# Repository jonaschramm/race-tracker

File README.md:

Custom PCB data logger for motorcycle racing: GPS position + IMU motion data,
logged to a microSD card, with an e-Paper status display. Built around an
ESP32-S3 (WiFi/BT built in) so it can also stream/sync over WiFi.

## Current version: V3 (ESP32-S3)

**This is the active, current board.** Everything else in this repo (see
[History / older versions](#history--older-versions) below) is superseded —
kept for reference only, not under active development.

```
RaceTracker.kicad_prj/V3 ESP32/RaceTracker_v3/RaceTracker_v3.kicad_pro
```

Open that project file in KiCad (10.0.5 or newer) — schematic
(`RaceTracker_v3.kicad_sch`) and PCB (`RaceTracker_v3.kicad_pcb`) are
alongside it.

### Status

- Schematic: ERC clean (0 violations).
- PCB: fully routed by hand, `kicad-cli pcb drc --severity-all` → 0 errors
  (a handful of expected warnings only — see below).
- Board: 4-layer, ~56×66mm with rounded corner bosses for 4× M2 mounting
  holes.
- BOM: all 44 parts have a manufacturer part number and LCSC code (or
  DigiKey, where LCSC doesn't carry the part) in the schematic symbol
  properties — see `bom/bom.csv`.

**Known, expected DRC warnings (not bugs):**
- `lib_footprint_mismatch` on J1, J5, J6, SW1, U1 — these footprints were
  deliberately hand-adjusted to match real component pad geometry (pulled
  from the parts' own datasheets/reference designs) rather than the stock
  KiCad library footprint. **Do not run "Update Footprint from Library" on
  these** — it would silently overwrite the verified geometry.

### Key components

| Function | Part |
|---|---|
| MCU (WiFi + BT) | ESP32-S3-WROOM-1-N8 (U1) |
| IMU (6-axis) | Würth WSEN-ISDS (U4) |
| GPS | external module via J3 (2.54mm header, I2C) — no onboard GPS |
| Storage | microSD (J4) |
| Display | e-Paper via J6 (8-pin header) |
| Charging | MCP73831 Li-Ion charger (U2) + USB-C (J1) |
| 3.3V rail | AP2112K-3.3 LDO (U3) |
| Debug | UART via J5 (4-pin header) |

Pin-header connectors (J3, J5, J6) have their pin functions silkscreened
next to each pin so nothing gets miswired when the board is in hand without
the schematic open.

### 3D preview

Rendered straight from the board file (`kicad-cli pcb render`). A ready-to-embed,
interactive 3D model (quantized GLB, 3.4 MB — Draco was tried first but needs an
external decoder that not every embedding context can reach) lives at
[`RaceTracker.kicad_prj/V3 ESP32/RaceTracker_v3/3d/RaceTracker_v3.glb`](RaceTracker.kicad_prj/V3%20ESP32/RaceTracker_v3/3d/RaceTracker_v3.glb) —
drop it into a [`<model-viewer>`](https://modelviewer.dev/) tag on any webpage to let
visitors spin the board around (also works in AR on phones). More stills in
`assets/renders/`.

### Open items

Not yet done — flagging so nothing is assumed finished:

1. **RF review** — the ESP32-S3's on-board antenna keepout is respected on
   the PCB, but nobody with hands-on RF experience has reviewed the
   placement. Espressif's own guideline calls for **≥15mm clearance between
   the antenna and any metal** (enclosure, shielding) — the two mounting
   holes closest to the antenna (top-left/top-right) are only ~3mm away, so
   **use nylon/plastic M2 screws there**, not metal.
2. **Enclosure / mechanical design** — no current mechanical spec for a
   case; board dimensions have changed several times, don't reuse an old one.
3. **3D models / "finished" 3D view** — not started.
4. Two BOM values are assumptions, not confirmed: D2/D3 LED colors (set to
   red/green — schematic didn't specify a color) and SW1's exact MPN
   (couldn't verify its physical dimensions against the datasheet).
5. 27 pads show as "no net" against the schematic's auto-generated
   placeholder nets — reviewed at a glance as genuinely-unused pins
   (GPIO headroom, USB SBU lines), not individually re-verified.

## Repo layout

```
RaceTracker.kicad_prj/
├── *.kicad_sch, RaceTracker.kicad_pcb   ← V1 (SAMD21 + onboard GPS/WiFi modules) — historical
├── V3 ESP32/RaceTracker_v3/             ← V3 (ESP32-S3) — CURRENT, see above
└── V3 ESP32/tools/                      ← pcbnew scripting helpers used while building V3
v2-simple/                                ← V2 (SAMD21, simplified, external GPS/WiFi) — abandoned mid-layout, superseded by V3
reference/eagle/                          ← imported Eagle symbols (Arduino MKR WiFi 1010) used as a source for V1/V2 parts
bom/bom.csv                               ← current BOM with MPN/LCSC/pricing data (V3)
```

### History / older versions

- **V1** (`RaceTracker.kicad_prj/*.kicad_sch` at the repo root, tag
  `v1-full`): original design — Arduino MKR WiFi 1010 (SAMD21) + separate
  u-blox ZED-F9P RTK GPS module + MPU-6050 IMU. Fully routed, but heavier
  and pricier than needed for the actual use case.
- **V2 / `v2-simple`**: a pivot to drop the onboard GPS/WiFi modules in
  favor of external pluggable headers, still on the SAMD21. Placement-only;
  routing was never finished before the project moved to V3's ESP32-S3
  (which has WiFi/BT built in, removing the need for a separate radio
  module entirely). Kept for reference; not maintained.

## Branches

`main` tracks the current state (V3). Historical exploration happened on
`v2-simple` — merged into `main` and not separately maintained going forward.

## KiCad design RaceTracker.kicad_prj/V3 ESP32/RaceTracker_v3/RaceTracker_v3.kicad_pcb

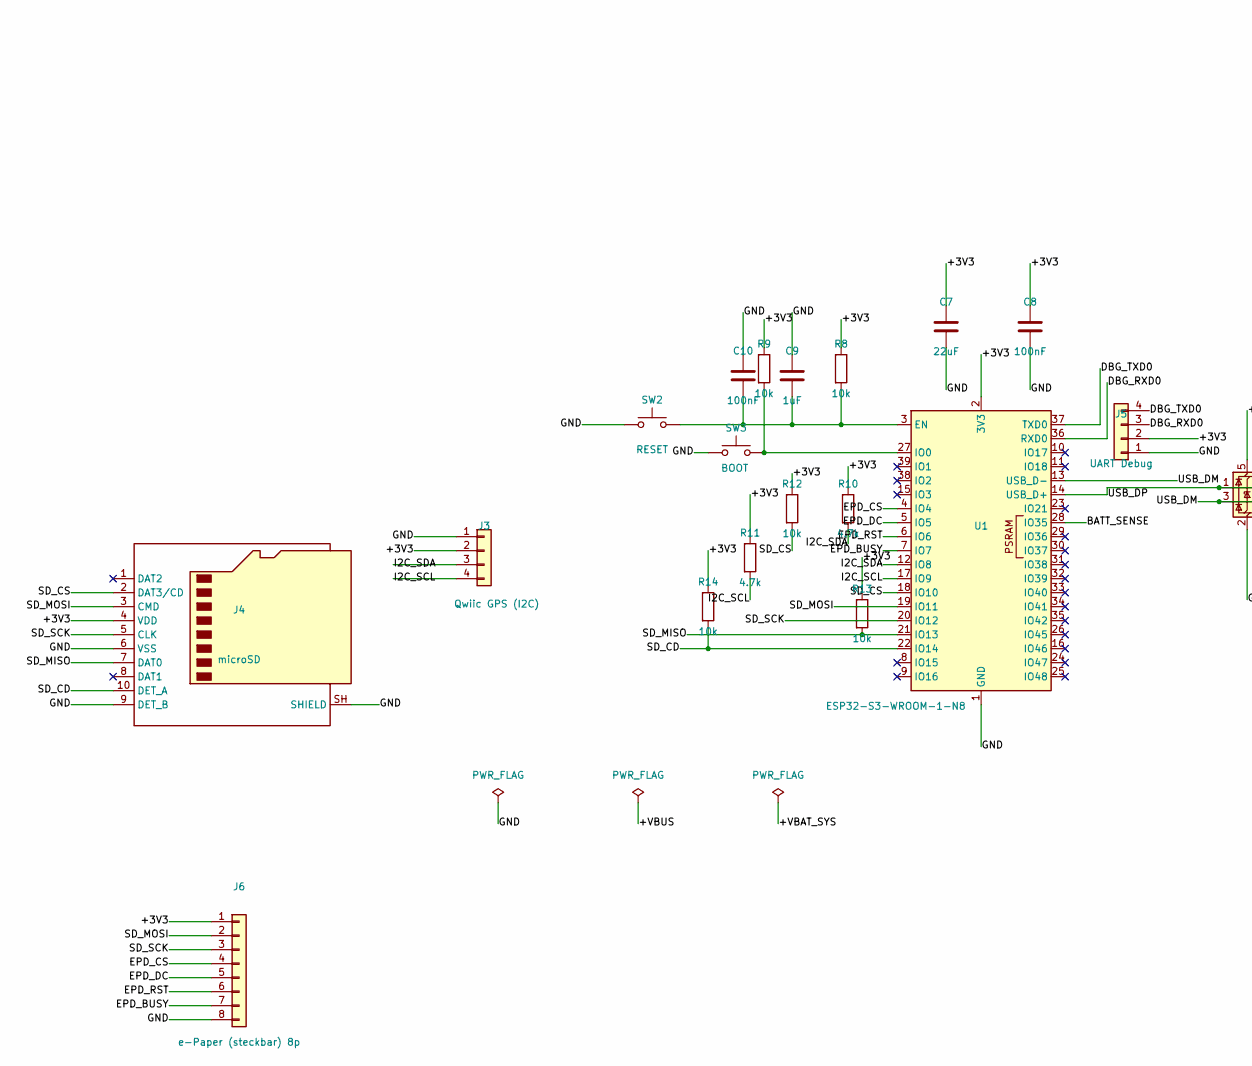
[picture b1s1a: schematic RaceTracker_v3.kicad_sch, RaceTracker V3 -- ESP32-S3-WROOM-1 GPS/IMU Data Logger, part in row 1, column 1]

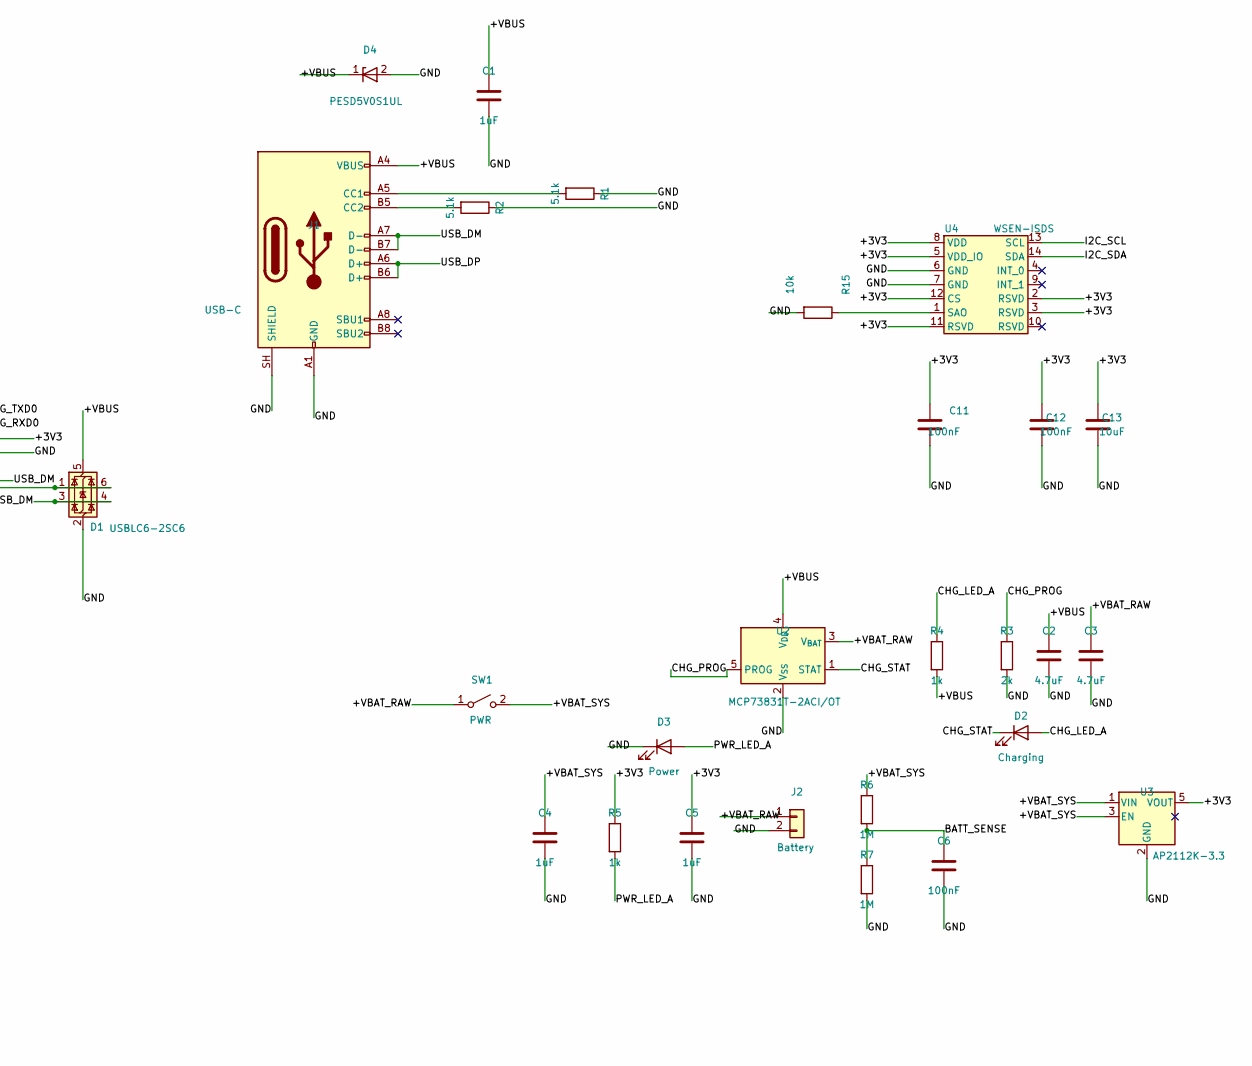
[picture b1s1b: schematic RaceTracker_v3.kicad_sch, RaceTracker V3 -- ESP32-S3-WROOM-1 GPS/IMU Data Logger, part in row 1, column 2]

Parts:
C1, C4, C5, C9: 1uF; C_0603_1608Metric; MPN CL10A105KB8NNNC; LCSC C15849
C2, C3: 4.7uF; C_0603_1608Metric; MPN CL10A475KO8NNNC; LCSC C19666
C6, C8, C10, C11, C12: 100nF; C_0603_1608Metric; MPN CC0603KRX7R9BB104; LCSC C14663
C7: 22uF; C_0805_2012Metric; MPN CL21A226MAQNNNE; LCSC C45783
C13: 10uF; C_0805_2012Metric; MPN CL21A106KAYNNNE; LCSC C15850
D1: USBLC6-2SC6; SOT-23-6; MPN USBLC6-2SC6; LCSC C2687116
D2: Charging; LED_0603_1608Metric; MPN XL-1608SURC-06; LCSC C965799
D3: Power; LED_0603_1608Metric; MPN XL-1608UGC-04; LCSC C965804
D4: PESD5V0S1UL; D_SOD-882; MPN PESD5V0S1UL; LCSC C85402
J1: USB-C; USB_C_Receptacle_HRO_TYPE-C-31-M-12; MPN TYPE-C-31-M-12; LCSC C165948
J2: Battery; JST_PH_S2B-PH-SM4-TB_1x02-1MP_P2.00mm_Horizontal; MPN S2B-PH-SM4-TB(LF)(SN); LCSC C295747
J3: Qwiic GPS (I2C); PinHeader_1x04_P2.54mm_Vertical; MPN PZ254V-11-04P; LCSC C2691448
J4: microSD; microSD_HC_Molex_104031-0811; MPN 104031-0811; LCSC C585350
J5: UART Debug; PinHeader_1x04_P2.54mm_Vertical; MPN PZ254V-11-04P; LCSC C2691448
J6: e-Paper (steckbar) 8p; PinHeader_1x08_P2.54mm_Vertical; MPN PZ254V-11-08P; LCSC C492407
R1, R2: 5.1k; R_0603_1608Metric; MPN 0603WAF5101T5E; LCSC C23186
R3: 2k; R_0603_1608Metric; MPN 0603WAF2001T5E; LCSC C22975
R4, R5: 1k; R_0603_1608Metric; MPN 0603WAF1001T5E; LCSC C21190
R6, R7: 1M; R_0603_1608Metric; MPN 0603WAF1004T5E; LCSC C22935
R8, R9, R12, R13, R14, R15: 10k; R_0603_1608Metric; MPN 0603WAF1002T5E; LCSC C25804
R10, R11: 4.7k; R_0603_1608Metric; MPN 0603WAF4701T5E; LCSC C23162
SW1: PWR; SW_DIP_SPSTx01_Slide_6.7x4.1mm_W7.62mm_P2.54mm_LowProfile; MPN DSWB01LHGET; LCSC C126888
SW2: RESET; SW_SPST_B3U-1000P; MPN B3U-1000P; LCSC C231329
SW3: BOOT; SW_SPST_B3U-1000P; MPN B3U-1000P; LCSC C231329
U1: ESP32-S3-WROOM-1-N8; ESP32-S3-WROOM-1; MPN ESP32-S3-WROOM-1-N8; LCSC C2913198
U2: MCP73831T-2ACI/OT; SOT-23-5; MPN MCP73831T-2ACI/OT; LCSC C424093
U3: AP2112K-3.3; SOT-23-5; MPN AP2112K-3.3TRG1; LCSC C23380830
U4: WSEN-ISDS; LGA-14_3x2.5mm_P0.5mm_LayoutBorder3x4y; MPN 2536030320001

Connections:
/+3V3: C5.1, C7.1, C8.1, C11.1, C12.1, C13.1, J3.2, J4.4 (VDD), J5.2, J6.1, R5.1, R8.1, R9.1, R10.1, R11.1, R12.1, R13.1, R14.1, U1.2 (3V3), U3.5 (VOUT), U4.2 (RSVD), U4.3 (RSVD), U4.5 (VDD_IO), U4.8 (VDD), U4.11 (RSVD), U4.12 (CS)
/+VBAT_RAW: C3.1, J2.1, SW1.1 (A), U2.3 (V_{BAT})
/+VBAT_SYS: C4.1, R6.1, SW1.2 (B), U3.1 (VIN), U3.3 (EN)
/+VBUS: C1.1, C2.1, D1.5 (VBUS), D4.1 (K), J1.A4 (VBUS), J1.A9 (VBUS), J1.B4 (VBUS), J1.B9 (VBUS), R4.2, U2.4 (V_{DD})
/BATT_SENSE: C6.1, R6.2, R7.1, U1.28 (IO35)
/CHG_LED_A: D2.2 (A), R4.1
/CHG_PROG: R3.1, U2.5 (PROG)
/CHG_STAT: D2.1 (K), U2.1 (STAT)
/DBG_RXD0: J5.3, U1.36 (RXD0)
/DBG_TXD0: J5.4, U1.37 (TXD0)
/EPD_BUSY: J6.7, U1.7 (IO7)
/EPD_CS: J6.4, U1.4 (IO4)
/EPD_DC: J6.5, U1.5 (IO5)
/EPD_RST: J6.6, U1.6 (IO6)
/GND: C1.2, C2.2, C3.2, C4.2, C5.2, C6.2, C7.2, C8.2, C9.1, C10.1, C11.2, C12.2, C13.2, D1.2 (GND), D3.1 (K), D4.2 (A), J1.A1 (GND), J1.A12 (GND), J1.B1 (GND), J1.B12 (GND), J1.SH (SHIELD), J2.2, J3.1, J4.6 (VSS), J4.9 (DET_B), J4.SH (SHIELD), J5.1, J6.8, R1.1, R2.1, R3.2, R7.2, R15.2, SW2.1, SW3.1, U1.1 (GND), U1.40 (GND), U1.41 (GND), U2.2 (V_{SS}), U3.2 (GND), U4.6 (GND), U4.7 (GND)
/I2C_SCL: J3.4, R11.2, U1.17 (IO9), U4.13 (SCL)
/I2C_SDA: J3.3, R10.2, U1.12 (IO8), U4.14 (SDA)
/PWR_LED_A: D3.2 (A), R5.2
/SD_CD: J4.10 (DET_A), R14.2, U1.22 (IO14)
/SD_CS: J4.2 (DAT3/CD), R12.2, U1.18 (IO10)
/SD_MISO: J4.7 (DAT0), R13.2, U1.21 (IO13)
/SD_MOSI: J4.3 (CMD), J6.2, U1.19 (IO11)
/SD_SCK: J4.5 (CLK), J6.3, U1.20 (IO12)
/USB_DM: D1.3 (I/O2), D1.4 (I/O2), J1.A7 (D-), J1.B7 (D-), U1.13 (USB_D-)
/USB_DP: D1.1 (I/O1), D1.6 (I/O1), J1.A6 (D+), J1.B6 (D+), U1.14 (USB_D+)
unnamed: J1.A5 (CC1), R1.2
unnamed: J1.B5 (CC2), R2.2
unnamed: C9.2, C10.2, R8.2, SW2.2, U1.3 (EN)
unnamed: R9.2, SW3.2, U1.27 (IO0)
unnamed: R15.1, U4.1 (SAO)

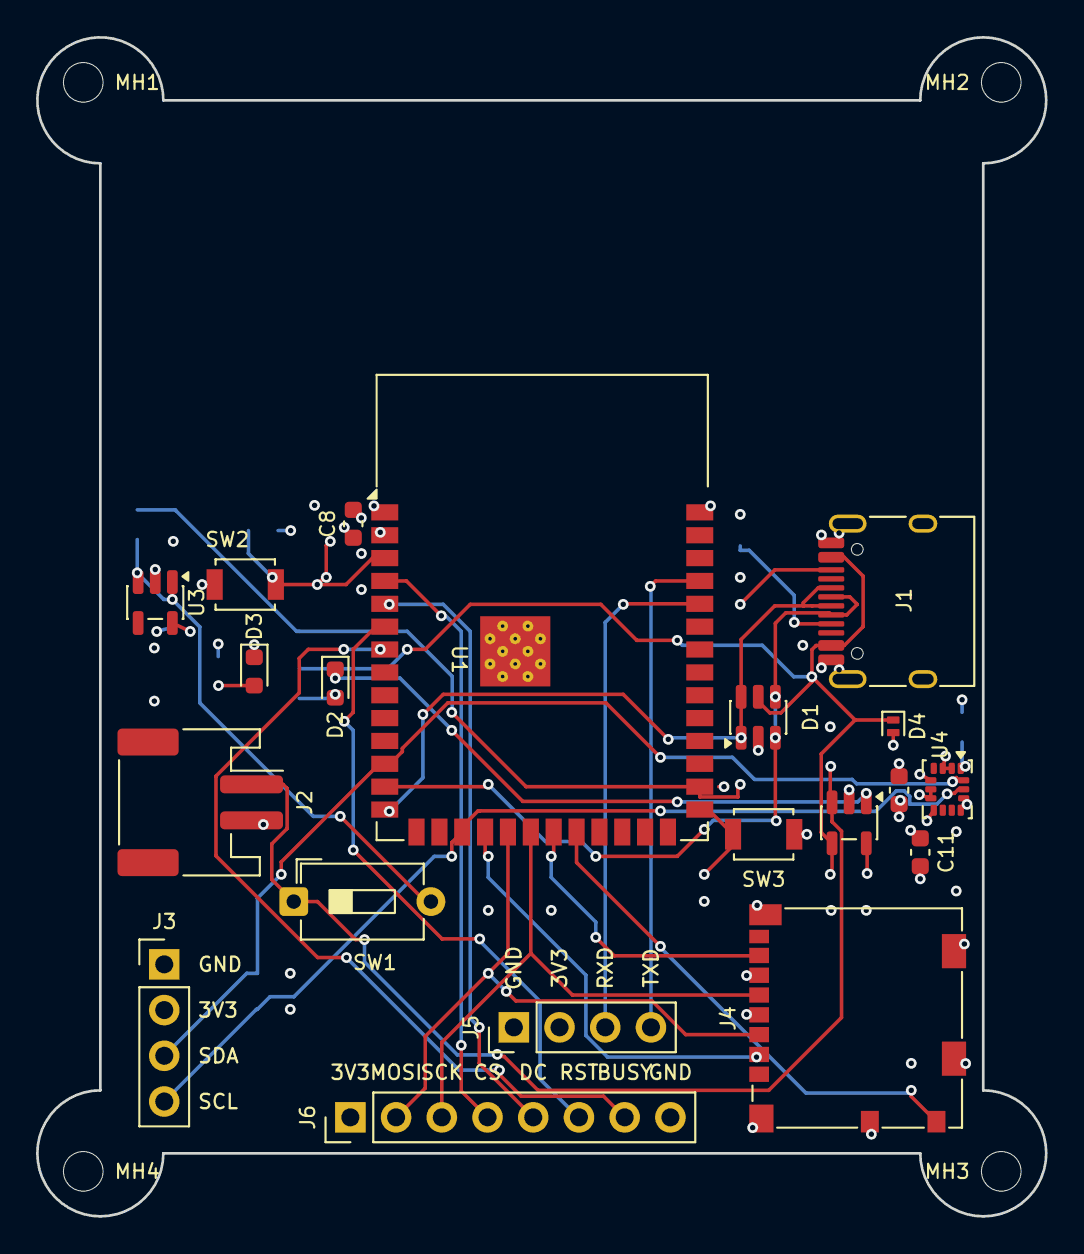
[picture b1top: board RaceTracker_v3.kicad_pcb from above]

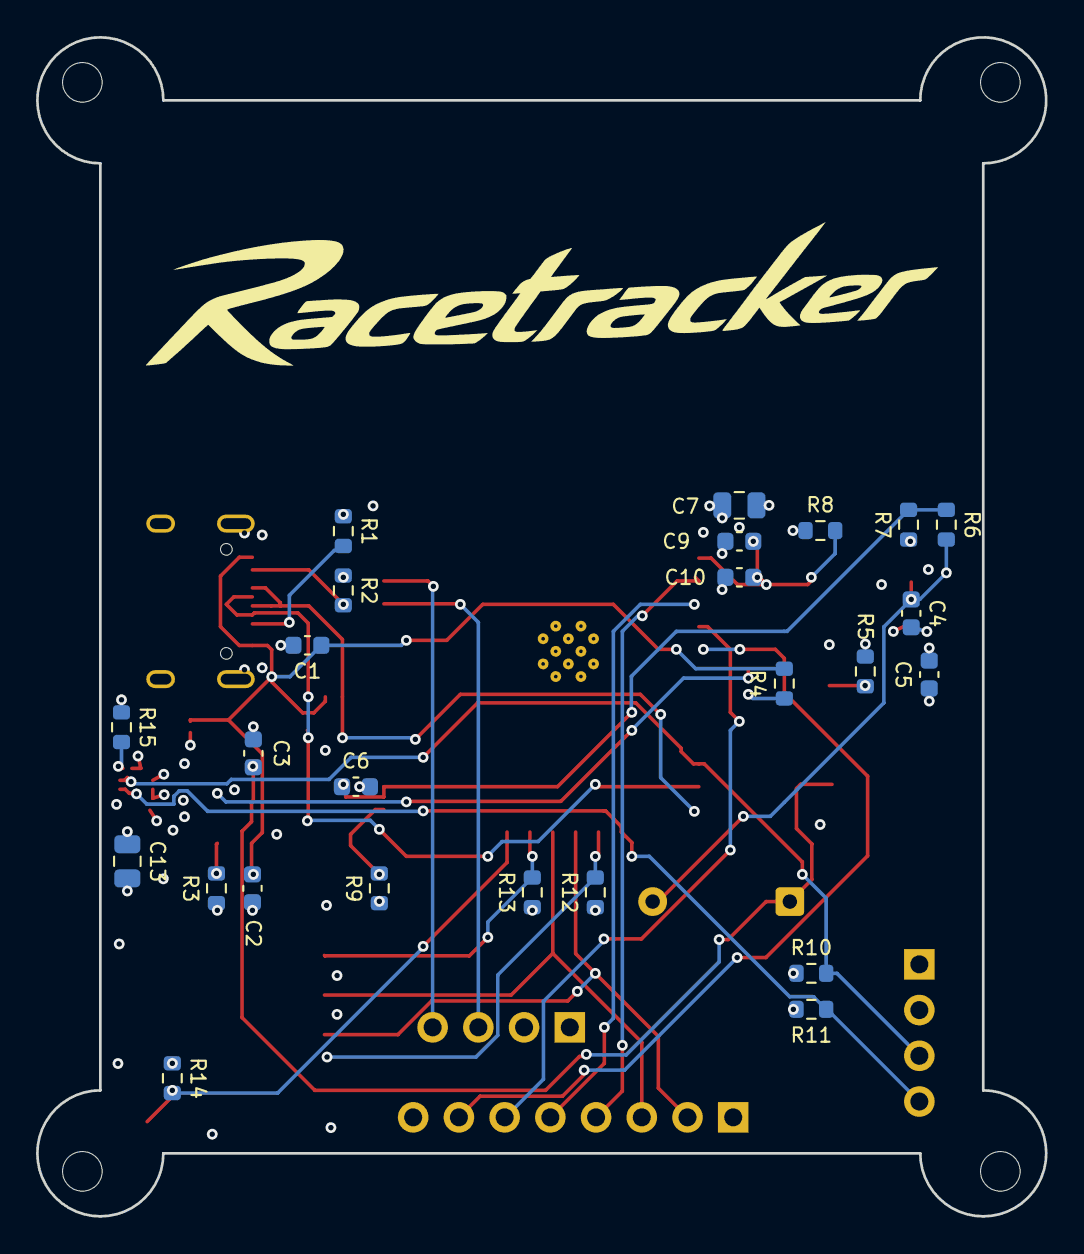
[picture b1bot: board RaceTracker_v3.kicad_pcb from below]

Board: 4 copper layers, 56.0 x 65.5 mm, 49 parts (25 on the bottom side), 30 nets.

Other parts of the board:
MH1, MH2, MH3, MH4: MountingHole_2.2mm_M2

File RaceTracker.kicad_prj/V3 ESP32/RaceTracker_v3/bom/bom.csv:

Reference,Qty,Value,Footprint,MPN,Manufacturer,LCSC,LC_Stock,Chosen_Distributor,Datasheet,Validated,DNP,Notes
"C1,C4,C9,C5",4,1uF,0603,CL10A105KB8NNNC,Samsung Electro-Mechanics,C15849,,,,,,
"C3,C2",2,4.7uF,0603,CL10A475KO8NNNC,Samsung Electro-Mechanics,C19666,,,,,,
C7,1,22uF,0805,CL21A226MAQNNNE,Samsung Electro-Mechanics,C45783,,,,,,
"C12,C10,C11,C6,C8",5,100nF,0603,CC0603KRX7R9BB104,Yageo,C14663,,,,,,
C13,1,10uF,0805,CL21A106KAYNNNE,Samsung Electro-Mechanics,C15850,,,,,,
D1,1,USBLC6-2SC6,SOT-23-6,USBLC6-2SC6,STMicroelectronics,C2687116,,,,,,
D2,1,Charging,0603,XL-1608SURC-06,XLSEMI (Chenzhixin),C965799,,,,,,
D3,1,Power,0603,XL-1608UGC-04,XLSEMI (Chenzhixin),C965804,,,,,,
D4,1,PESD5V0S1UL,SOD-882,PESD5V0S1UL,Nexperia,C85402,,,,,,
J1,1,USB-C,USB_C_Receptacle_HRO_TYPE-C-31-M-12,TYPE-C-31-M-12,Korean Hroparts Elec,C165948,,,,,,
J2,1,Battery,JST_PH_S2B-PH-SM4-TB_1x02-1MP_P2.00mm_Horizontal,S2B-PH-SM4-TB(LF)(SN),JST,C295747,,,,,,
J3,1,Qwiic GPS (I2C),PinHeader_1x04_P2.54mm_Vertical,PZ254V-11-04P,BOOMELE,C2691448,,,,,,
J4,1,microSD,microSD_HC_Molex_104031-0811,104031-0811,Molex,C585350,,,,,,
J5,1,UART Debug,PinHeader_1x04_P2.54mm_Vertical,PZ254V-11-04P,BOOMELE,C2691448,,,,,,
J6,1,e-Paper (steckbar) 8p,PinHeader_1x08_P2.54mm_Vertical,PZ254V-11-08P,BOOMELE,C492407,,,,,,
"R2,R1",2,5.1k,0603,0603WAF5101T5E,Uniroyal Elec,C23186,,,,,,
R3,1,2k,0603,0603WAF2001T5E,Uniroyal Elec,C22975,,,,,,
"R5,R4",2,1k,0603,0603WAF1001T5E,Uniroyal Elec,C21190,,,,,,
"R7,R6",2,1M,0603,0603WAF1004T5E,Uniroyal Elec,C22935,,,,,,
"R9,R14,R15,R13,R12,R8",6,10k,0603,0603WAF1002T5E,Uniroyal Elec,C25804,,,,,,
"R10,R11",2,4.7k,0603,0603WAF4701T5E,Uniroyal Elec,C23162,,,,,,
SW1,1,PWR,SW_DIP_SPSTx01_Slide_6.7x4.1mm_W7.62mm_P2.54mm_LowProfile,DSWB01LHGET,DECIGN,C126888,,,,,,
SW2,1,RESET,SW_SPST_B3U-1000P,B3U-1000P,Omron,C231329,,,,,,
SW3,1,BOOT,SW_SPST_B3U-1000P,B3U-1000P,Omron,C231329,,,,,,
U1,1,ESP32-S3-WROOM-1-N8,ESP32-S3-WROOM-1,ESP32-S3-WROOM-1-N8,Espressif Systems,C2913198,,,,,,
U2,1,MCP73831T-2ACI/OT,SOT-23-5,MCP73831T-2ACI/OT,Microchip Technology,C424093,,,,,,
U3,1,AP2112K-3.3,SOT-23-5,AP2112K-3.3TRG1,Diodes Incorporated,C23380830,,,,,,
U4,1,WSEN-ISDS,LGA-14_3x2.5mm_P0.5mm_LayoutBorder3x4y,2536030320001,Wuerth Elektronik,,,,https://www.we-online.com/components/products/datasheet/2536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,,,

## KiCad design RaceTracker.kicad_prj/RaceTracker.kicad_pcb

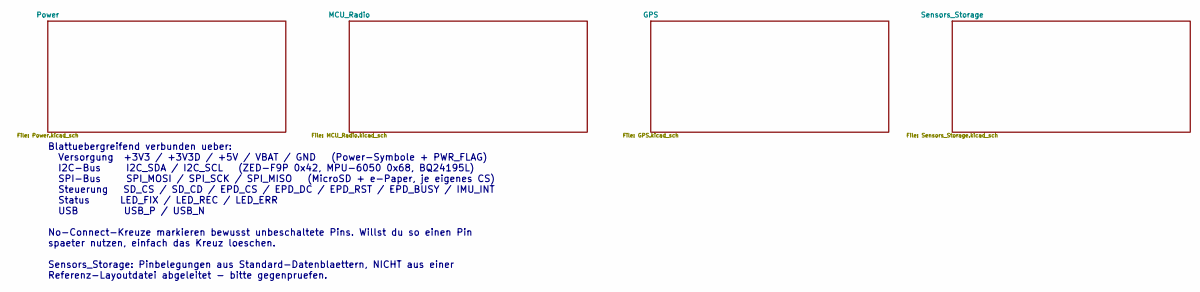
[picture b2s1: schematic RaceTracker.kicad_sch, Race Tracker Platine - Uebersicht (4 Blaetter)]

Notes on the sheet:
Blattuebergreifend verbunden ueber: Versorgung +3V3 / +3V3D / +5V / VBAT / GND (Power-Symbole + PWR_FLAG) I2C-Bus I2C_SDA / I2C_SCL (ZED-F9P 0x42, MPU-6050 0x68, BQ24195L) SPI-Bus SPI_MOSI / SPI_SCK / SPI_MISO (MicroSD + e-Paper, je eigenes CS) Steuerung SD_CS / SD_CD / EPD_CS / EPD_DC / EPD_RST / 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

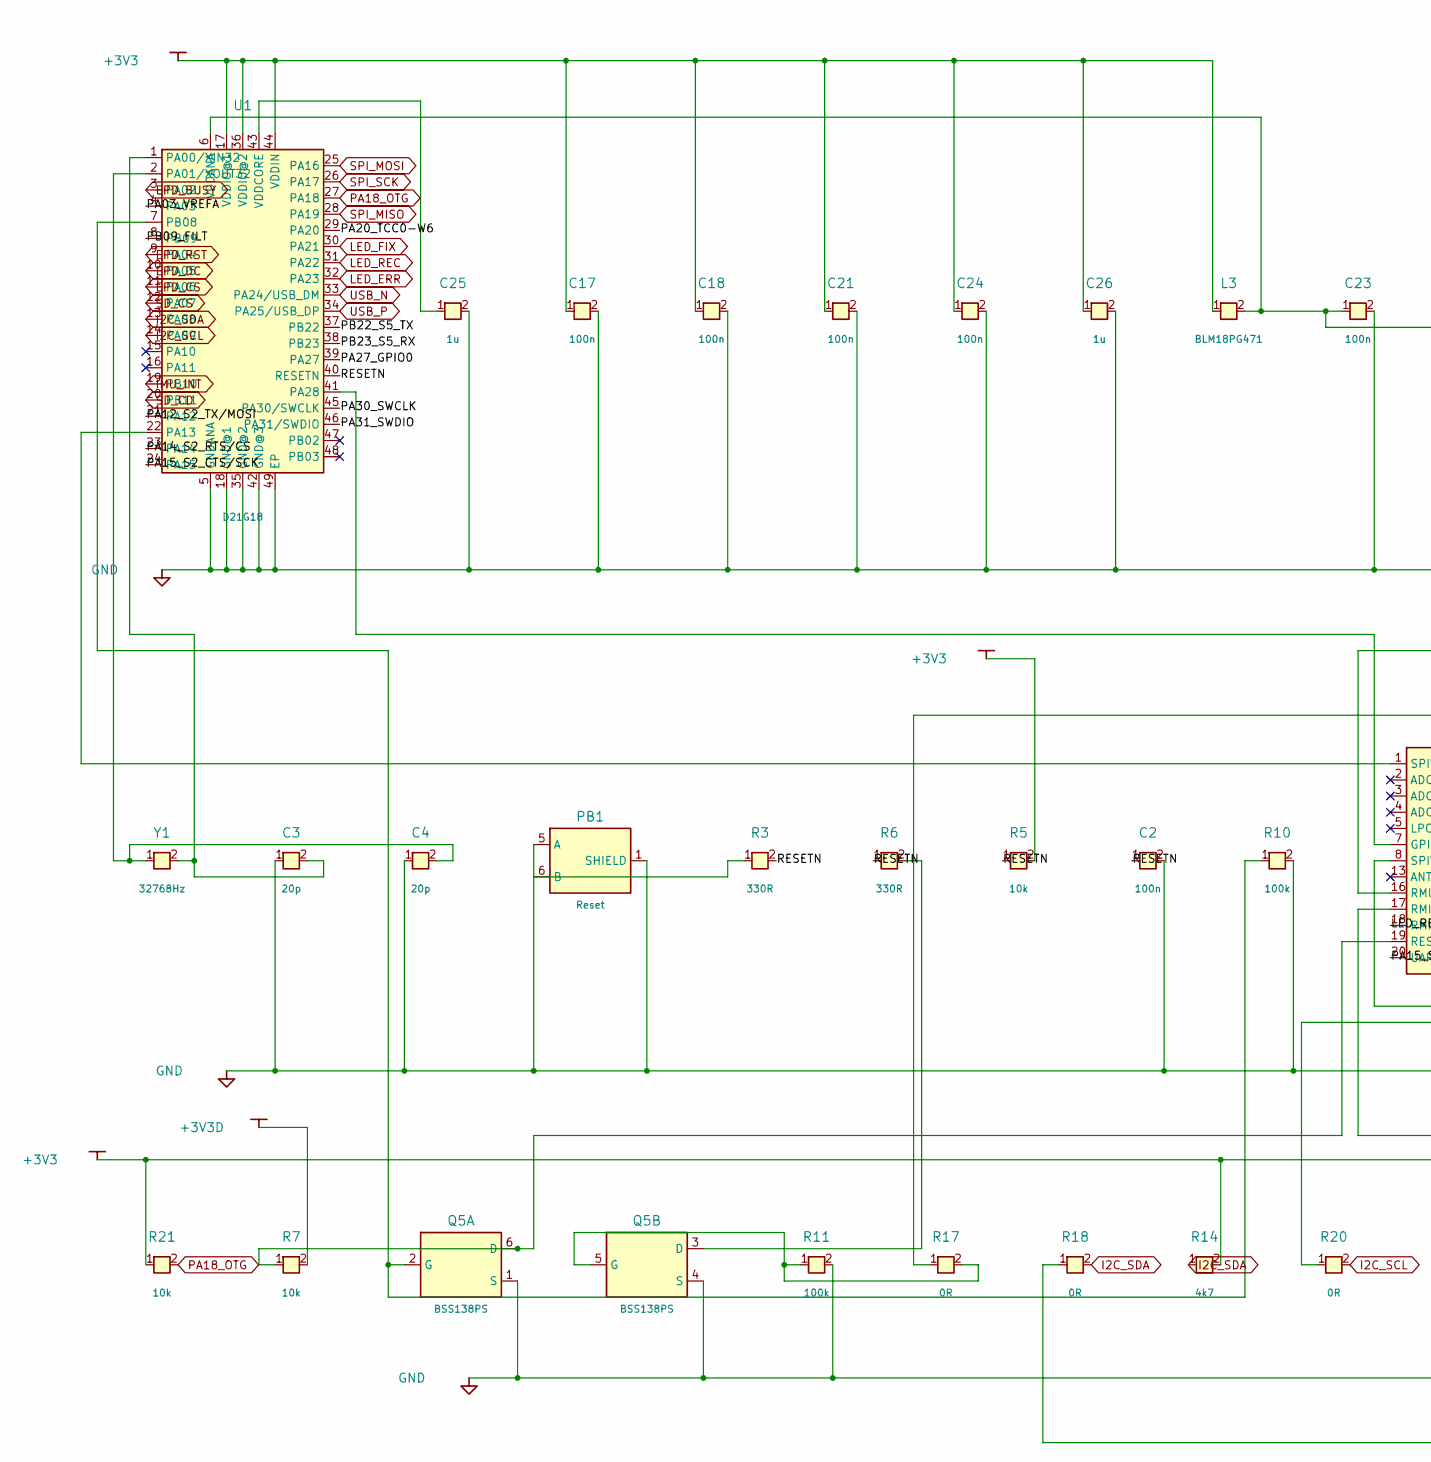
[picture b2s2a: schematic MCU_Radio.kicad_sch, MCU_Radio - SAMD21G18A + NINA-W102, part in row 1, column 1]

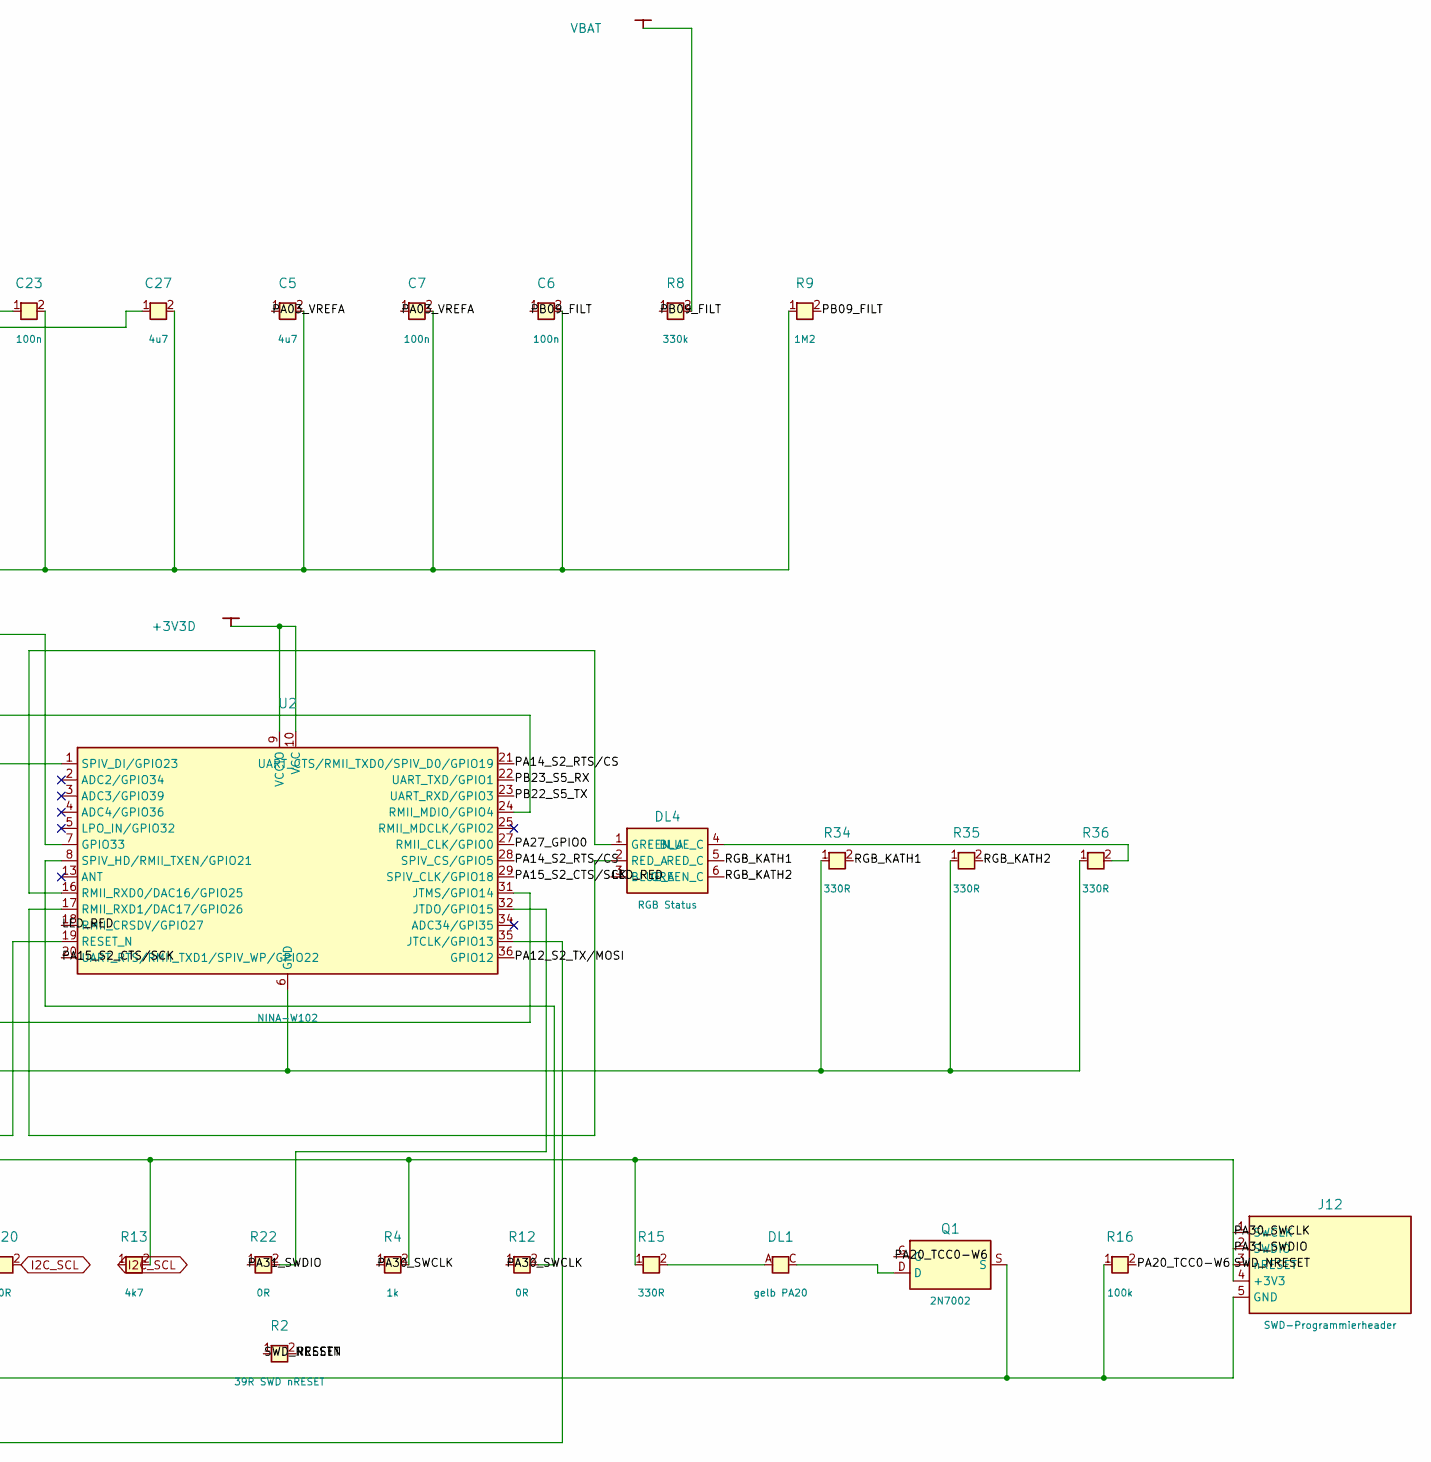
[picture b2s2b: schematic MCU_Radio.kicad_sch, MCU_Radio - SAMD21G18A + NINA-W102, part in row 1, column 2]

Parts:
C2, C6, C7, C17, C18, C21, C23, C24: 100n; C_0402_1005Metric
C3, C4: 20p; C_0402_1005Metric
C5: 4u7; C_0402_1005Metric
C25, C26: 1u; C_0402_1005Metric
C27: 4u7; C_0603_1608Metric
DL1: gelb PA20; LED_0603_AK
DL4: RGB Status; RGBLED_5050
J12: SWD-Programmierheader; PinHeader_1x05_P2.54mm_Vertical
L3: BLM18PG471; L_0603_1608Metric
PB1: Reset; PTS820_NO_HOLES
Q1: 2N7002; SOTFL50P160X78-3
Q5: BSS138PS; SOT363
R2: 39R SWD nRESET; R_0402_1005Metric
R3, R6, R15, R34, R35, R36: 330R; R_0402_1005Metric
R4: 1k; R_0402_1005Metric
R5, R7, R21: 10k; R_0402_1005Metric
R8: 330k; R_0402_1005Metric
R9: 1M2; R_0402_1005Metric
R10, R11, R16: 100k; R_0402_1005Metric
R12, R17, R18, R20, R22: 0R; R_0402_1005Metric
R13, R14: 4k7; R_0402_1005Metric
U1: D21G18; QFN48_SAMD21G18A
U2: NINA-W102; NINA_W1X_MODULE
Y1: 32768Hz; ABS07_CRYSTAL

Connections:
+3V3D: R7.2, U2.9 (VCCIO), U2.10 (VCC); also elsewhere on the board
/MCU_Radio/LED_RED: DL4.3 (BLUE_A), U2.18 (RMII_CRSDV/GPIO27)
/MCU_Radio/PA03_VREFA: C5.1, C7.1, U1.4 (PA03)
/MCU_Radio/PA12_S2_TX/MOSI: U1.21 (PA12), U2.36 (GPIO12)
/MCU_Radio/PA14_S2_RTS/CS: U1.23 (PA14), U2.21 (UART_CTS/RMII_TXD0/SPIV_D0/GPIO19), U2.28 (SPIV_CS/GPIO5)
/MCU_Radio/PA15_S2_CTS/SCK: U1.24 (PA15), U2.20 (UART_RTS/RMII_TXD1/SPIV_WP/GPIO22), U2.29 (SPIV_CLK/GPIO18)
/MCU_Radio/PA20_TCC0-W6: Q1.G, R16.2, U1.29 (PA20)
/MCU_Radio/PA27_GPIO0: U1.39 (PA27), U2.27 (RMII_CLK/GPIO0)
/MCU_Radio/PB09_FILT: C6.1, R8.1, R9.2, U1.8 (PB09)
/MCU_Radio/PB22_S5_TX: U1.37 (PB22), U2.23 (UART_RXD/GPIO3)
/MCU_Radio/PB23_S5_RX: U1.38 (PB23), U2.22 (UART_TXD/GPIO1)
/MCU_Radio/RESETN: C2.1, R2.2, R3.2, R5.1, R6.1, U1.40 (RESETN)
/MCU_Radio/RGB_KATH1: DL4.5 (RED_C), R34.2
/MCU_Radio/RGB_KATH2: DL4.6 (GREEN_C), R35.2
EPD_BUSY: U1.3 (PA02); also elsewhere on the board
EPD_CS: U1.11 (PA06); also elsewhere on the board
EPD_DC: U1.10 (PA05); also elsewhere on the board
EPD_RST: U1.9 (PA04); also elsewhere on the board
GND: C2.2, C3.1, C4.1, C5.2, C6.2, C7.2, C17.2, C18.2, C21.2, C23.2, C24.2, C25.2, C26.2, C27.2, J12.5 (GND), PB1.1 (SHIELD), PB1.2 (SHIELD), PB1.3 (SHIELD), PB1.4 (SHIELD), PB1.5 (A), Q1.S, Q5.1 (S), Q5.4 (S), R9.1, R10.2, R11.2, R16.1, R34.1, R35.1, R36.1, U1.5 (GNDANA), U1.18 (GND@1), U1.35 (GND@2), U1.42 (GND@3), U1.49 (EP), U2.6 (GND), U2.12, U2.14, U2.26, U2.30, U2.GND@1, U2.GND@2, U2.GND@3, U2.GND@4, U2.GND@5, U2.GND@6, U2.GND@7, U2.GND@8, U2.GND@9, U2.GND@10, U2.GND@11, U2.GND@12; also elsewhere on the board
I2C_SCL: R13.1, R20.2, U1.14 (PA09); also elsewhere on the board
I2C_SDA: R14.1, R18.2, U1.13 (PA08); also elsewhere on the board
IMU_INT: U1.19 (PB10); also elsewhere on the board
LED_ERR: U1.32 (PA23); also elsewhere on the board
LED_FIX: U1.30 (PA21); also elsewhere on the board
LED_REC: U1.31 (PA22); also elsewhere on the board
unnamed: DL1.A, R15.2
unnamed: DL1.C, Q1.D
unnamed: DL4.4 (BLUE_C), R36.2
unnamed: DL4.1 (GREEN_A), U2.16 (RMII_RXD0/DAC16/GPIO25)
unnamed: DL4.2 (RED_A), U2.17 (RMII_RXD1/DAC17/GPIO26)
unnamed: PB1.6 (B), R3.1
unnamed: Q5.6 (D), R7.1, U2.19 (RESET_N)
unnamed: Q5.2 (G), R10.1, U1.7 (PB08)
unnamed: Q5.3 (D), R6.2
unnamed: Q5.5 (G), R11.1, R17.2
unnamed: C3.2, U1.1 (PA00/XIN32), Y1.2
unnamed: C4.2, U1.2 (PA01/XOUT32), Y1.1
unnamed: U1.22 (PA13), U2.1 (SPIV_DI/GPIO23)
unnamed: U1.41 (PA28), U2.7 (GPIO33)
unnamed: C23.1, C27.1, L3.2, U1.6 (VDDANA)
unnamed: C25.1, U1.43 (VDDCORE)
unnamed: R18.1, U2.35 (JTCLK/GPIO13)
unnamed: R22.2, U2.32 (JTDO/GPIO15)
unnamed: R20.1, U2.31 (JTMS/GPIO14)
unnamed: R17.1, U2.24 (RMII_MDIO/GPIO4)
unnamed: R12.2, U2.8 (SPIV_HD/RMII_TXEN/GPIO21)
PA18_OTG: R21.2, U1.27 (PA18); also elsewhere on the board
SD_CD: U1.20 (PB11); also elsewhere on the board
SD_CS: U1.12 (PA07); also elsewhere on the board
SPI_MISO: U1.28 (PA19); also elsewhere on the board
SPI_MOSI: U1.25 (PA16); also elsewhere on the board
SPI_SCK: U1.26 (PA17); also elsewhere on the board
USB_P: U1.34 (PA25/USB_DP); also elsewhere on the board
VBAT: R8.2; also elsewhere on the board
